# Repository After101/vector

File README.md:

# vector

  This is a custom wearable I'm working on that uses the nRF52840 featuring:
  - BLE
  - Gesture based controls
  - ST7789 raw OLED panel
  - Haptic feedback
  - Custom enclosure
  - Magnetic pogo pin charging and programming
  -  29mm x 20mm PCB 
  -  Enclosure WIP

  Current status:
  - PCB complete
  - Enclosure WIP
  - Firmware not done yet

  This is a revision of my previous project lol
  
  Images:
  
  4 layer PCB finally

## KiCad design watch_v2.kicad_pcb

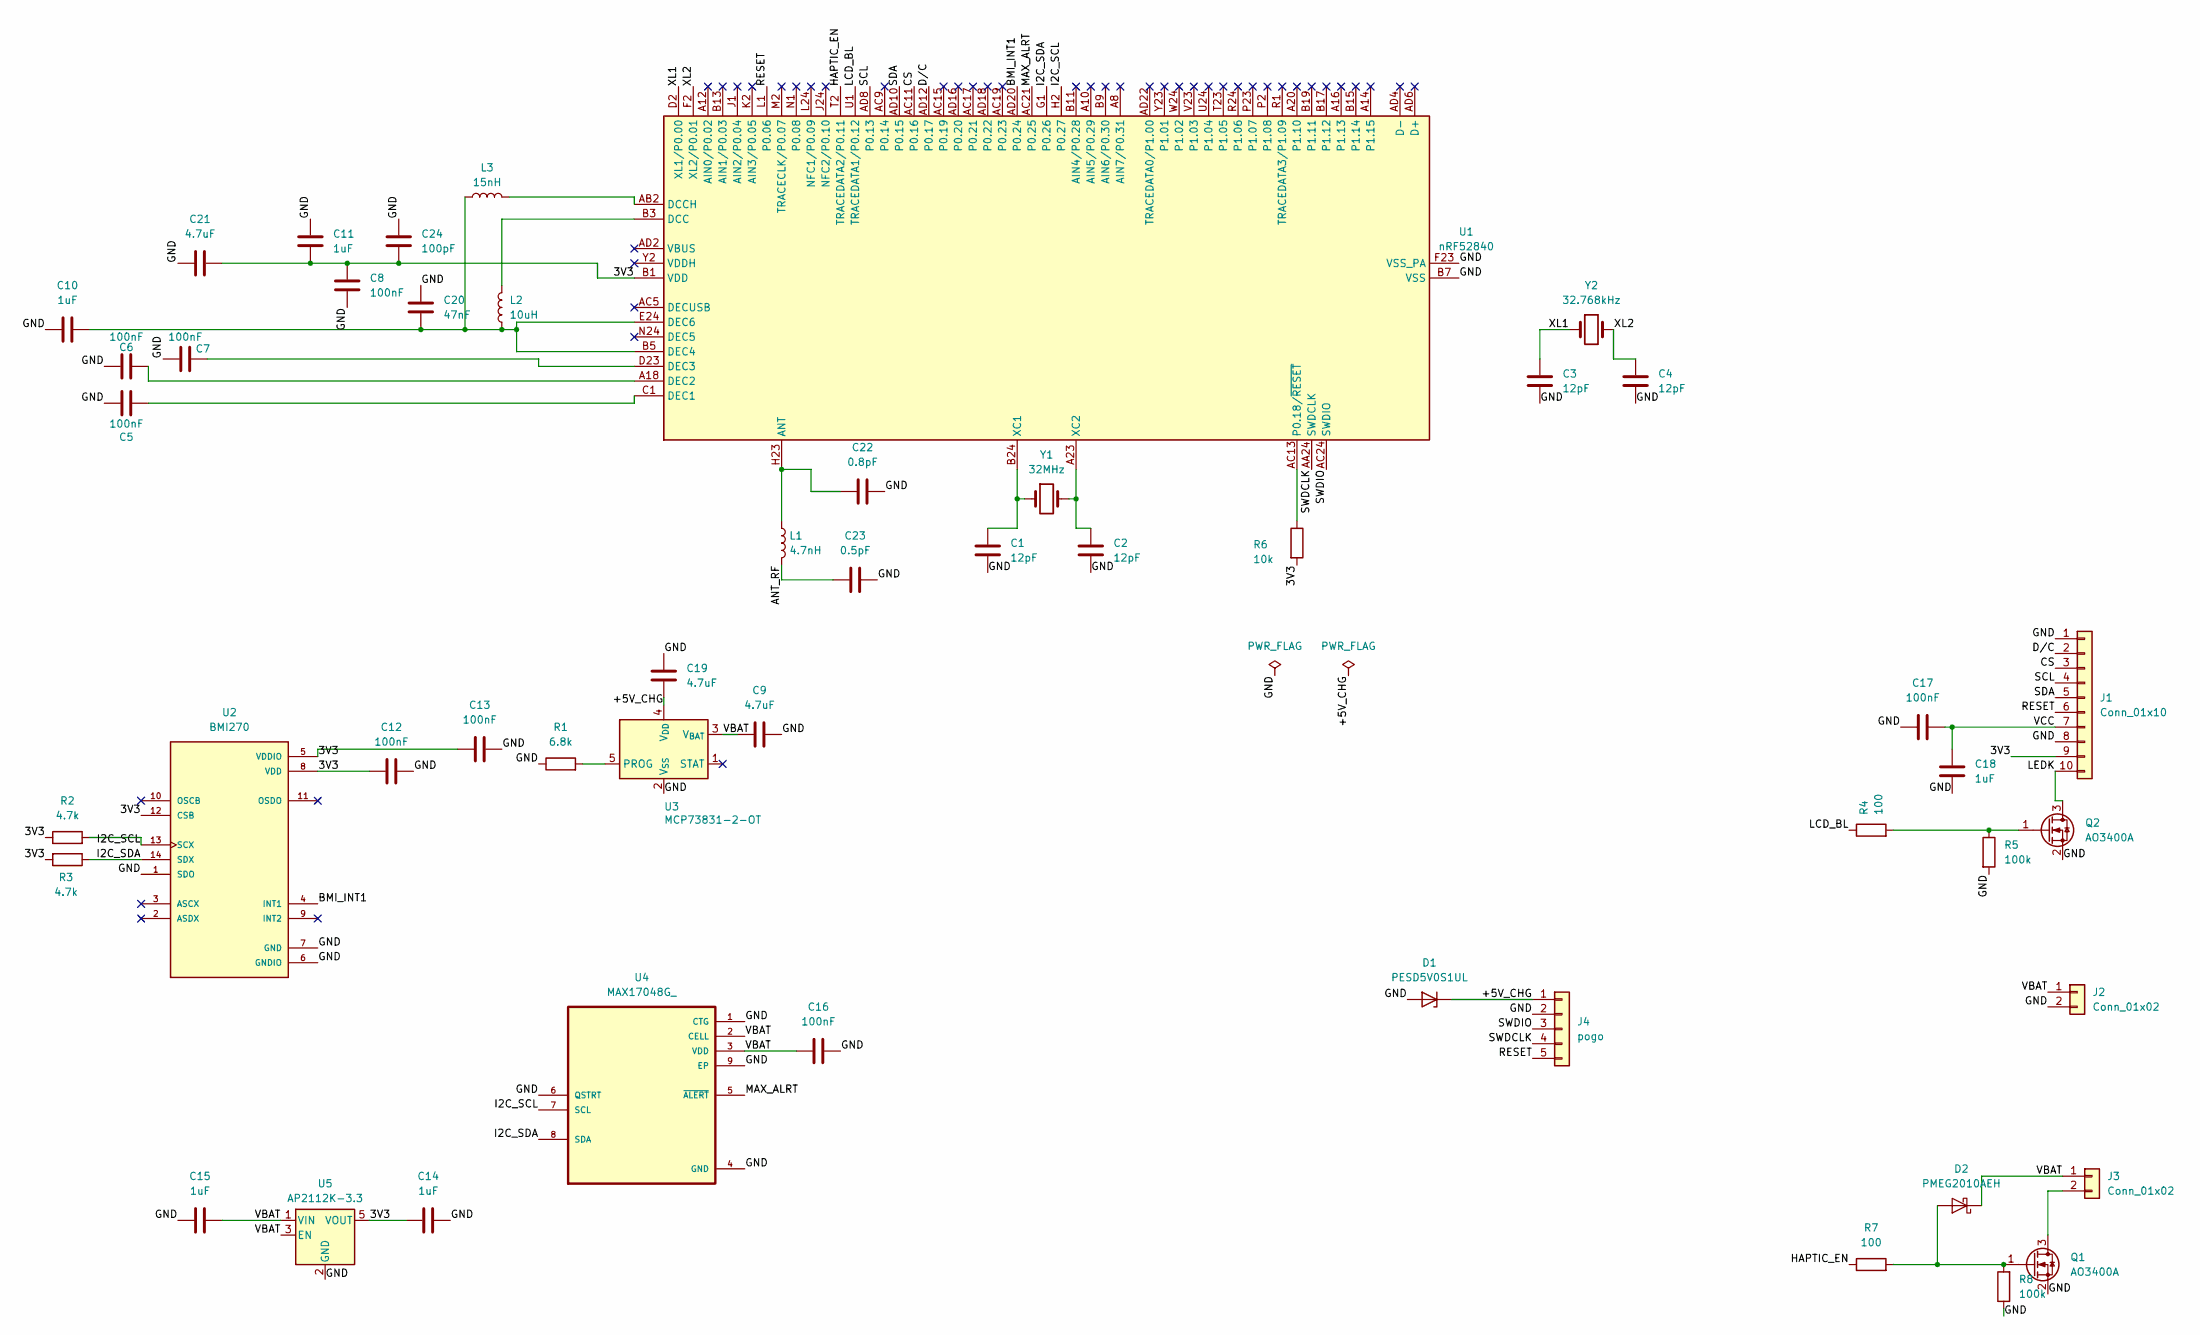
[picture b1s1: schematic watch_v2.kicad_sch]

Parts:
C1, C2, C3, C4: 12pF; C_0402_1005Metric
C5, C6, C7, C8, C12, C13, C16, C17: 100nF; C_0402_1005Metric
C9, C19, C21: 4.7uF; C_0603_1608Metric
C10, C11, C14, C15, C18: 1uF; C_0603_1608Metric
C20: 47nF; C_0402_1005Metric
C22: 0.8pF; C_0402_1005Metric
C23: 0.5pF; C_0402_1005Metric
C24: 100pF; C_0402_1005Metric
D1: PESD5V0S1UL; D_SOD-882
D2: PMEG2010AEH; D_SOD-123F
J1: Conn_01x10; Amphenol_F32Q-1A7x1-11010_1x10-1MP_P0.5mm_Horizontal
J2, J3: Conn_01x02; BATTERY_2P_SOLDER
J4: pogo; pogo pin
L1: 4.7nH; L_0402_1005Metric
L2: 10uH; L_0603_1608Metric
L3: 15nH; L_0402_1005Metric
Q1, Q2: AO3400A; SOT-23
R1: 6.8k; R_0402_1005Metric
R2, R3: 4.7k; R_0402_1005Metric
R4, R7: 100; R_0402_1005Metric
R5, R8: 100k; R_0402_1005Metric
R6: 10k; R_0402_1005Metric
U1: nRF52840; Nordic_AQFN-73-1EP_7x7mm_P0.5mm
U2: BMI270; XDCR_BMI270
U3: MCP73831-2-OT; SOT-23-5
U4: MAX17048G_; SON50P200X200X80-9N
U5: AP2112K-3.3; SOT-23-5
Y1: 32MHz; Crystal_SMD_2016-4Pin_2.0x1.6mm
Y2: 32.768kHz; Crystal_SMD_3215-2Pin_3.2x1.5mm

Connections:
/3V3: C8.2, C11.2, C12.1, C13.1, C14.1, C21.2, C24.2, J1.9, R2.1, R3.2, R6.2, U1.A22 (VDD), U1.AD14 (VDD), U1.AD23 (VDD), U1.B1 (VDD), U1.W1 (VDD), U2.5 (VDDIO), U2.8 (VDD), U2.12 (CSB), U5.5 (VOUT)
/+5V_CHG: C19.1, D1.1 (K), J4.1, U3.4 (V_{DD})
/ANT_RF: C23.1, L1.2
/BMI_INT1: U1.AD20 (P0.24), U2.4 (INT1)
/CS: J1.3, U1.AC11 (P0.16)
/D/C: J1.2, U1.AD12 (P0.17)
/GND: C1.2, C2.2, C3.2, C4.2, C5.1, C6.1, C7.1, C8.1, C9.2, C10.1, C11.1, C12.2, C13.2, C14.2, C15.1, C16.2, C17.1, C18.1, C19.2, C20.1, C21.1, C22.2, C23.2, C24.1, D1.2 (A), J1.1, J1.8, J2.2, J4.2, Q1.2 (S), Q2.2 (S), R1.1, R5.2, R8.1, U1.B7 (VSS), U1.EP (VSS), U1.F23 (VSS_PA), U2.1 (SDO), U2.6 (GNDIO), U2.7 (GND), U3.2 (V_{SS}), U4.1 (CTG), U4.4 (GND), U4.6 (QSTRT), U4.9 (EP), U5.2 (GND)
/HAPTIC_EN: R7.1, U1.T2 (TRACEDATA2/P0.11)
/I2C_SCL: R2.2, U1.H2 (P0.27), U2.13 (SCX), U4.7 (SCL)
/I2C_SDA: R3.1, U1.G1 (P0.26), U2.14 (SDX), U4.8 (SDA)
/LCD_BL: R4.1, U1.U1 (TRACEDATA1/P0.12)
/LEDK: J1.10, Q2.3 (D)
/MAX_ALRT: U1.AC21 (P0.25), U4.5 (~ALERT)
/RESET: J1.6, J4.5, U1.L1 (P0.06)
/SCL: J1.4, U1.AD8 (P0.13)
/SDA: J1.5, U1.AD10 (P0.15)
/SWDCLK: J4.4, U1.AA24 (SWDCLK)
/SWDIO: J4.3, U1.AC24 (SWDIO)
/VBAT: C9.1, C15.2, C16.1, D2.1 (K), J2.1, J3.1, U3.3 (V_{BAT}), U4.2 (CELL), U4.3 (VDD), U5.1 (VIN), U5.3 (EN)
/VCC: C17.2, C18.2, J1.7
/XL1: C3.1, U1.D2 (XL1/P0.00), Y2.1
/XL2: C4.1, U1.F2 (XL2/P0.01), Y2.2
unnamed: D2.2 (A), Q1.1 (G), R7.2, R8.2
unnamed: J3.2, Q1.3 (D)
unnamed: Q2.1 (G), R4.2, R5.1
unnamed: C22.1, L1.1, U1.H23 (ANT)
unnamed: L2.2, U1.B3 (DCC)
unnamed: L3.2, U1.AB2 (DCCH)
unnamed: C5.2, U1.C1 (DEC1)
unnamed: C6.2, U1.A18 (DEC2)
unnamed: C7.2, U1.D23 (DEC3)
unnamed: C10.2, C20.2, L2.1, L3.1, U1.B5 (DEC4), U1.E24 (DEC6)
unnamed: R6.1, U1.AC13 (P0.18/~RESET)
unnamed: C1.1, U1.B24 (XC1), Y1.1
unnamed: C2.1, U1.A23 (XC2), Y1.2
unnamed: R1.2, U3.5 (PROG)

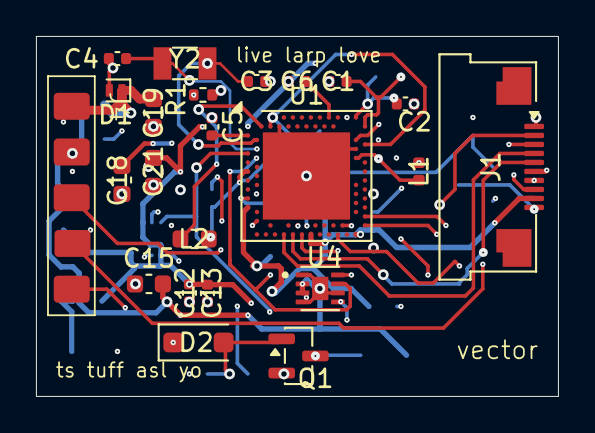
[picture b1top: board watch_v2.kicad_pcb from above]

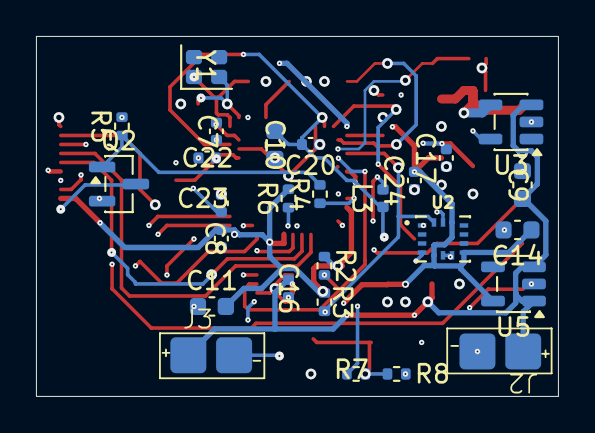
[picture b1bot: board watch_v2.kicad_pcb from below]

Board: 4 copper layers, 29.0 x 20.0 mm, 50 parts (27 on the bottom side), 36 nets.

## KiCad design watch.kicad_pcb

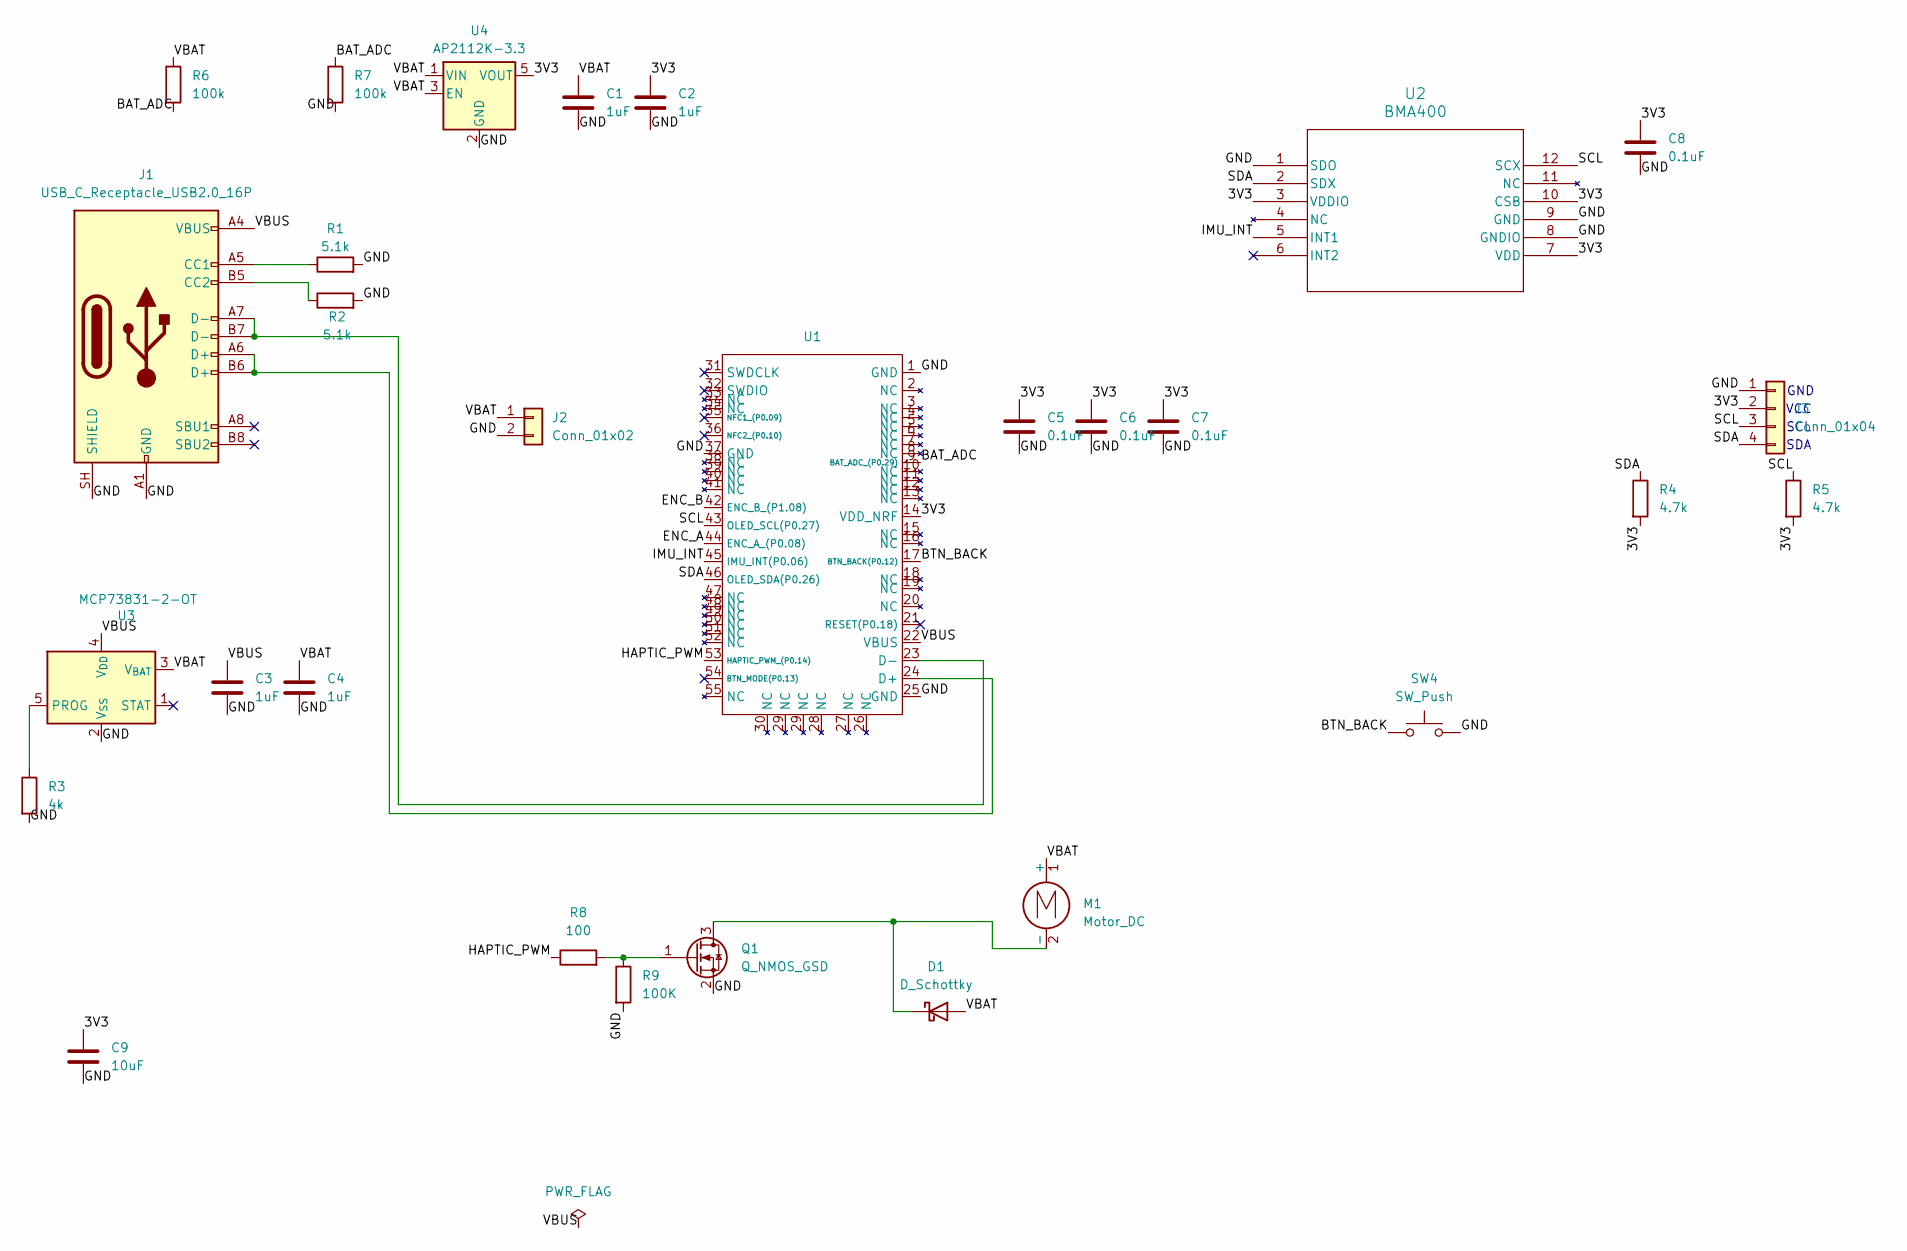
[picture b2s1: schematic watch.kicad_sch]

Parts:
C1, C2, C3, C4: 1uF; C_0603_1608Metric
C5, C6, C7, C8: 0.1uF; C_0603_1608Metric
C9: 10uF; C_0603_1608Metric
D1: D_Schottky; D_SOD-123
J1: USB_C_Receptacle_USB2.0_16P; USB_C_Receptacle_GCT_USB4105-xx-A_16P_TopMnt_Horizontal
J2: Conn_01x02; PinHeader_1x02_P1.00mm_Vertical
J3: Conn_01x04; PinHeader_1x04_P1.27mm_Vertical
M1: Motor_DC; SolderWire-0.5sqmm_1x02_P4.6mm_D0.9mm_OD2.1mm
Q1: Q_NMOS_GSD; SOT-23
R1, R2: 5.1k; R_0603_1608Metric
R3: 4k; R_0603_1608Metric
R4, R5: 4.7k; R_0603_1608Metric
R6, R7: 100k; R_0603_1608Metric
R8: 100; R_0603_1608Metric
R9: 100K; R_0603_1608Metric
SW4: SW_Push; SW_SPST_SKQG_WithoutStem
U1: ISC_nRF52840_A
U2: BMA400; QFN_BMA400_BOS
U3: MCP73831-2-OT; SOT-23-5
U4: AP2112K-3.3; SOT-23-5

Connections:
/3V3: C2.1, C5.1, C6.1, C7.1, C8.1, C9.1, J3.2, R4.2, R5.2, U1.14 (VDD_NRF), U2.3 (VDDIO), U2.7 (VDD), U2.10 (CSB), U4.5 (VOUT)
/BAT_ADC: R6.2, R7.1, U1.9 (BAT_ADC_(P0.29))
/BTN_BACK: SW4.1, U1.17 (BTN_BACK(P0.12))
/ENC_A: U1.44 (ENC_A_(P0.08))
/ENC_B: U1.42 (ENC_B_(P1.08))
/GND: C1.2, C2.2, C3.2, C4.2, C5.2, C6.2, C7.2, C8.2, C9.2, J1.A1 (GND), J1.A12 (GND), J1.B1 (GND), J1.B12 (GND), J1.SH (SHIELD), J2.2, J3.1, Q1.2 (S), R1.2, R2.2, R3.2, R7.2, R9.2, SW4.2, U1.1 (GND), U1.25 (GND), U1.37 (GND), U2.1 (SDO), U2.8 (GNDIO), U2.9 (GND), U3.2 (V_{SS}), U4.2 (GND)
/HAPTIC_PWM: R8.1, U1.53 (HAPTIC_PWM_(P0.14))
/IMU_INT: U1.45 (IMU_INT(P0.06)), U2.5 (INT1)
/SCL: J3.3, R5.1, U1.43 (OLED_SCL(P0.27)), U2.12 (SCX)
/SDA: J3.4, R4.1, U1.46 (OLED_SDA(P0.26)), U2.2 (SDX)
/VBAT: C1.1, C4.1, D1.2 (A), J2.1, M1.1 (+), R6.1, U3.3 (V_{BAT}), U4.1 (VIN), U4.3 (EN)
/VBUS: C3.1, J1.A4 (VBUS), J1.A9 (VBUS), J1.B4 (VBUS), J1.B9 (VBUS), U1.22 (VBUS), U3.4 (V_{DD})
unnamed: D1.1 (K), M1.2 (-), Q1.3 (D)
unnamed: J1.A5 (CC1), R1.1
unnamed: J1.B5 (CC2), R2.1
unnamed: Q1.1 (G), R8.2, R9.1
unnamed: J1.A6 (D+), J1.B6 (D+), U1.24 (D+)
unnamed: J1.A7 (D-), J1.B7 (D-), U1.23 (D-)
unnamed: R3.1, U3.5 (PROG)

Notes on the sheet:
VCC
GND
SDA
SCL

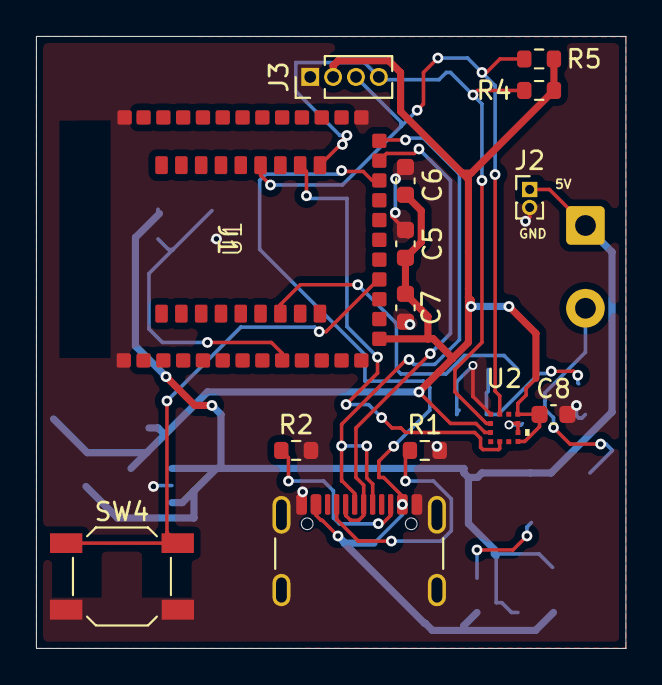
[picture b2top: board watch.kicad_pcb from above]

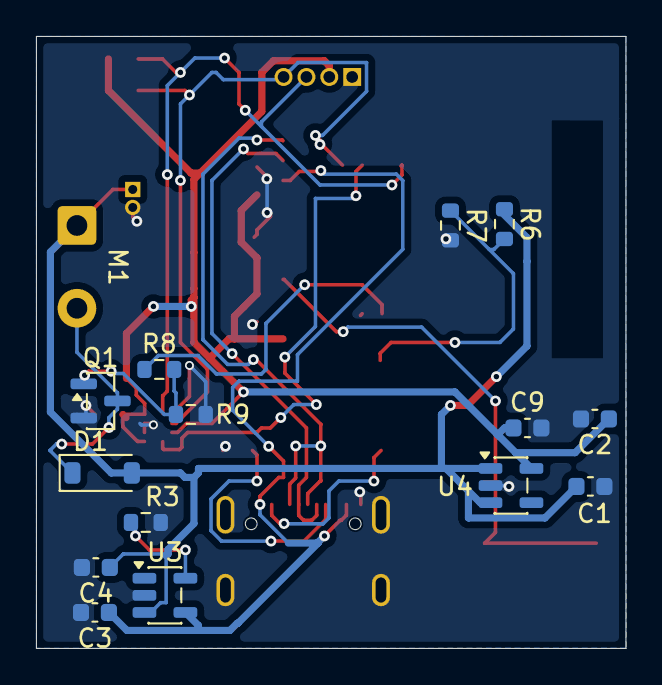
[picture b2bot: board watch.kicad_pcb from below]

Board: 2 copper layers, 32.8 x 34.0 mm, 29 parts (15 on the bottom side), 17 nets.
